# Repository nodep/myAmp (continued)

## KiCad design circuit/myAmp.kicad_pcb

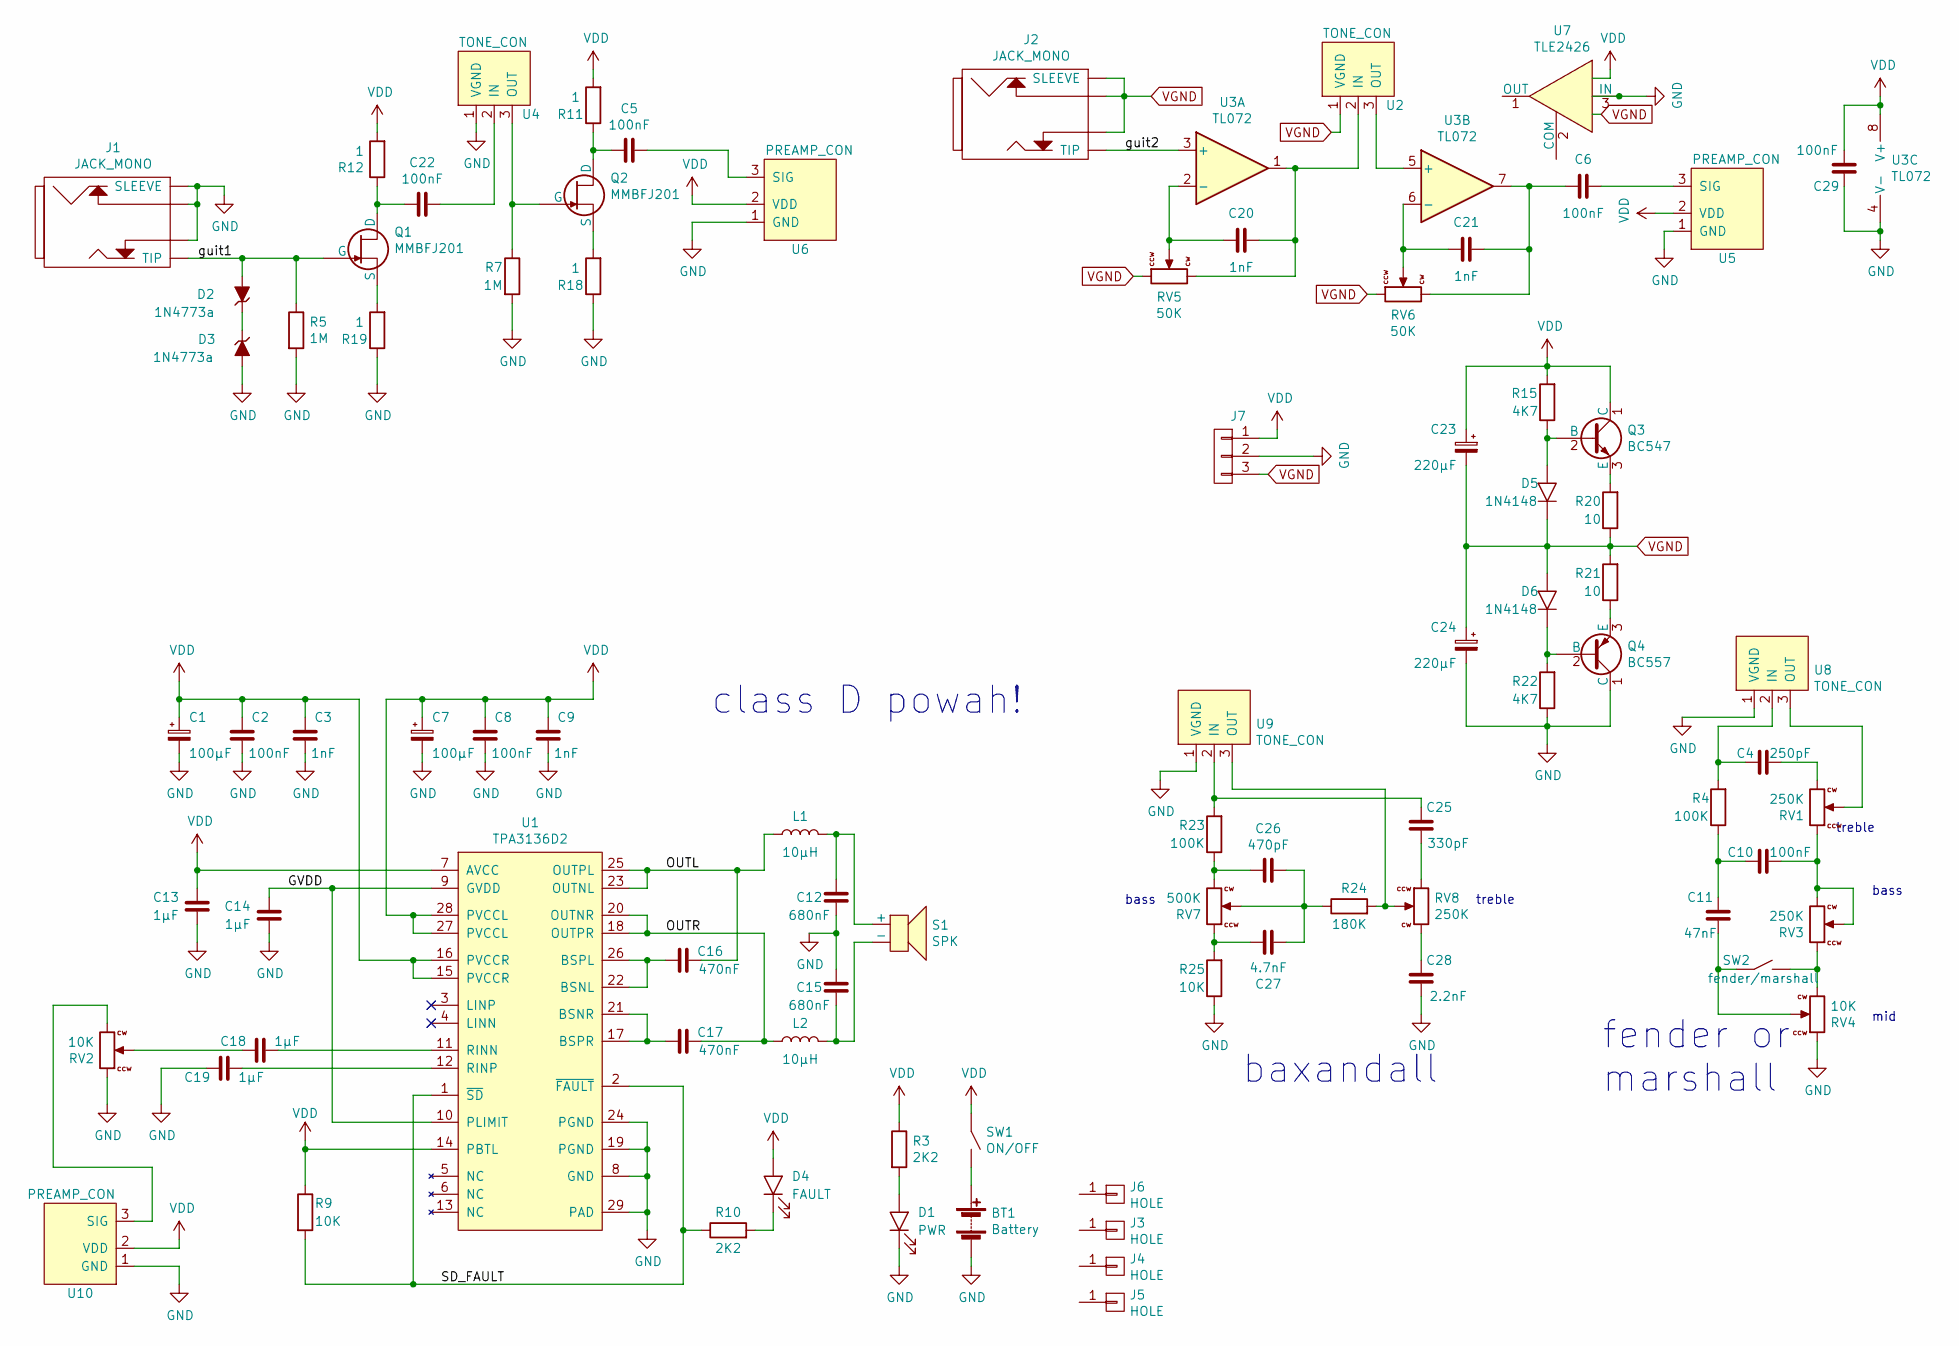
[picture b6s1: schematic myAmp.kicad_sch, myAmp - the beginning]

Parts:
BT1: Battery; BATTERY
C1, C7: 100μF; CPOL_D6.3_P2.5
C2, C8: 100nF; C_1206
C3, C9: 1nF; C_1206
C4: 250pF; C_5MM_1206
C5, C6, C10, C22, C29: 100nF; C_5MM_1206
C11: 47nF; C_5MM_1206
C12, C15: 680nF; C_FILM_5MM
C13, C14, C18, C19: 1μF; C_1206
C16, C17: 470nF; C_1206
C20, C21: 1nF; C_5MM_1206
C23, C24: 220μF; CPOL_D6.3_P2.5
C25: 330pF; C_5MM_1206
C26: 470pF; C_5MM_1206
C27: 4.7nF; C_5MM_1206
C28: 2.2nF; C_5MM_1206
D1: PWR; LED_D3.0mm
D2, D3: 1N4773a; DO41
D4: FAULT; LED_D3.0mm
D5, D6: 1N4148; DO35
J1, J2: JACK_MONO; JACK_CL13106
J3, J4, J5, J6: HOLE; MountingHole
J7: CONN_01X03; SPLITTER
L1, L2: 10μH; COILCRAFT_DR0810
Q1, Q2: MMBFJ201; SOT-23
Q3: BC547; TO-92_Inline_Wide
Q4: BC557; TO-92_Inline_Wide
R3, R10: 2K2; R_0805
R4, R23: 100K; R_10MM
R5, R7: 1M; R_10MM
R9: 10K; R_0805
R11, R12, R18, R19: 1; R_10MM
R15, R22: 4K7; R_0805
R20, R21: 10; R_0805
R24: 180K; R_10MM
R25: 10K; R_10MM
RV1, RV3, RV8: 250K; POT_VULGARIS
RV2, RV4: 10K; POT_VULGARIS
RV5, RV6: 50K; RPOT_RKT6V
RV7: 500K; POT_VULGARIS
S1: SPK; SPKR_5MM
SW1: ON/OFF; SW_TINY
SW2: fender/marshall; JUMPER
U1: TPA3136D2; HTSSOP-28_4.4x9.7mm_Pitch0.65mm_ThermalPad
U2, U4, U8, U9: TONE_CON
U3: TL072; SOIC-8_3.9x4.9mm_P1.27mm
U5, U6, U10: PREAMP_CON
U7: TLE2426; TO-92_Inline_Wide

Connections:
/GVDD: C14.1, U1.9 (GVDD), U1.10 (PLIMIT)
/OUTL: C16.1, L1.1, U1.23 (OUTNL), U1.25 (OUTPL)
/OUTR: C17.1, L2.1, U1.18 (OUTPR), U1.20 (OUTNR)
/SD_FAULT: R9.2, R10.1, U1.1 (~SD), U1.2 (~FAULT)
/guit1: D2.2 (A), J1.6 (TIP), Q1.3 (G), R5.1
/guit2: J2.6 (TIP), U3.3 (+)
unnamed: BT1.1 (+), SW1.2
unnamed: C4.1, RV1.3
unnamed: C4.2, R4.2, U8.2 (IN)
unnamed: C5.1, U6.3 (SIG)
unnamed: C5.2, Q2.1 (D), R11.1
unnamed: C6.1, U5.3 (SIG)
unnamed: C10.1, RV1.1, RV3.2, RV3.3
unnamed: C10.2, C11.2, R4.1
unnamed: C11.1, RV4.2, SW2.1
unnamed: C12.2, L1.2, S1.1 (+)
unnamed: C15.1, L2.2, S1.2 (-)
unnamed: C16.2, U1.22 (BSNL), U1.26 (BSPL)
unnamed: C17.2, U1.17 (BSPR), U1.21 (BSNR)
unnamed: C18.1, U1.11 (RINN)
unnamed: C18.2, RV2.2
unnamed: C19.1, U1.12 (RINP)
unnamed: C20.1, RV5.3, U2.2 (IN), U3.1
unnamed: C20.2, RV5.2, U3.2 (-)
unnamed: C6.2, C21.1, RV6.3, U3.7
unnamed: C21.2, RV6.2, U3.6 (-)
unnamed: C22.1, U4.2 (IN)
unnamed: C22.2, Q1.1 (D), R12.1
unnamed: C25.1, R23.2, U9.2 (IN)
unnamed: C25.2, RV8.1
unnamed: C26.1, C27.2, R24.1, RV7.2
unnamed: C26.2, R23.1, RV7.3
unnamed: C27.1, R25.2, RV7.1
unnamed: C28.1, RV8.3
unnamed: D1.2 (A), R3.2
unnamed: D2.1 (K), D3.1 (K)
unnamed: D4.1 (K), R10.2
unnamed: D5.2 (A), Q3.2 (B), R15.1
unnamed: D6.1 (K), Q4.2 (B), R22.2
unnamed: Q1.2 (S), R19.2
unnamed: Q2.2 (S), R18.2
unnamed: Q2.3 (G), R7.1, U4.3 (OUT)
unnamed: Q3.3 (E), R20.2
unnamed: Q4.3 (E), R21.1
unnamed: R24.2, RV8.2, U9.3 (OUT)
unnamed: RV1.2, U8.3 (OUT)
unnamed: RV2.3, U10.3 (SIG)
unnamed: RV3.1, RV4.3, SW2.2
unnamed: U2.3 (OUT), U3.5 (+)
VGND: C23.2, C24.1, D5.1 (K), D6.2 (A), J2.1, J2.3, J2.4 (SLEEVE), J7.3, R20.1, R21.2, RV5.1, RV6.1, U2.1 (VGND), U7.1 (OUT)

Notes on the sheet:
baxandall
class D powah!
bass
fender or marshall
mid
treble

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
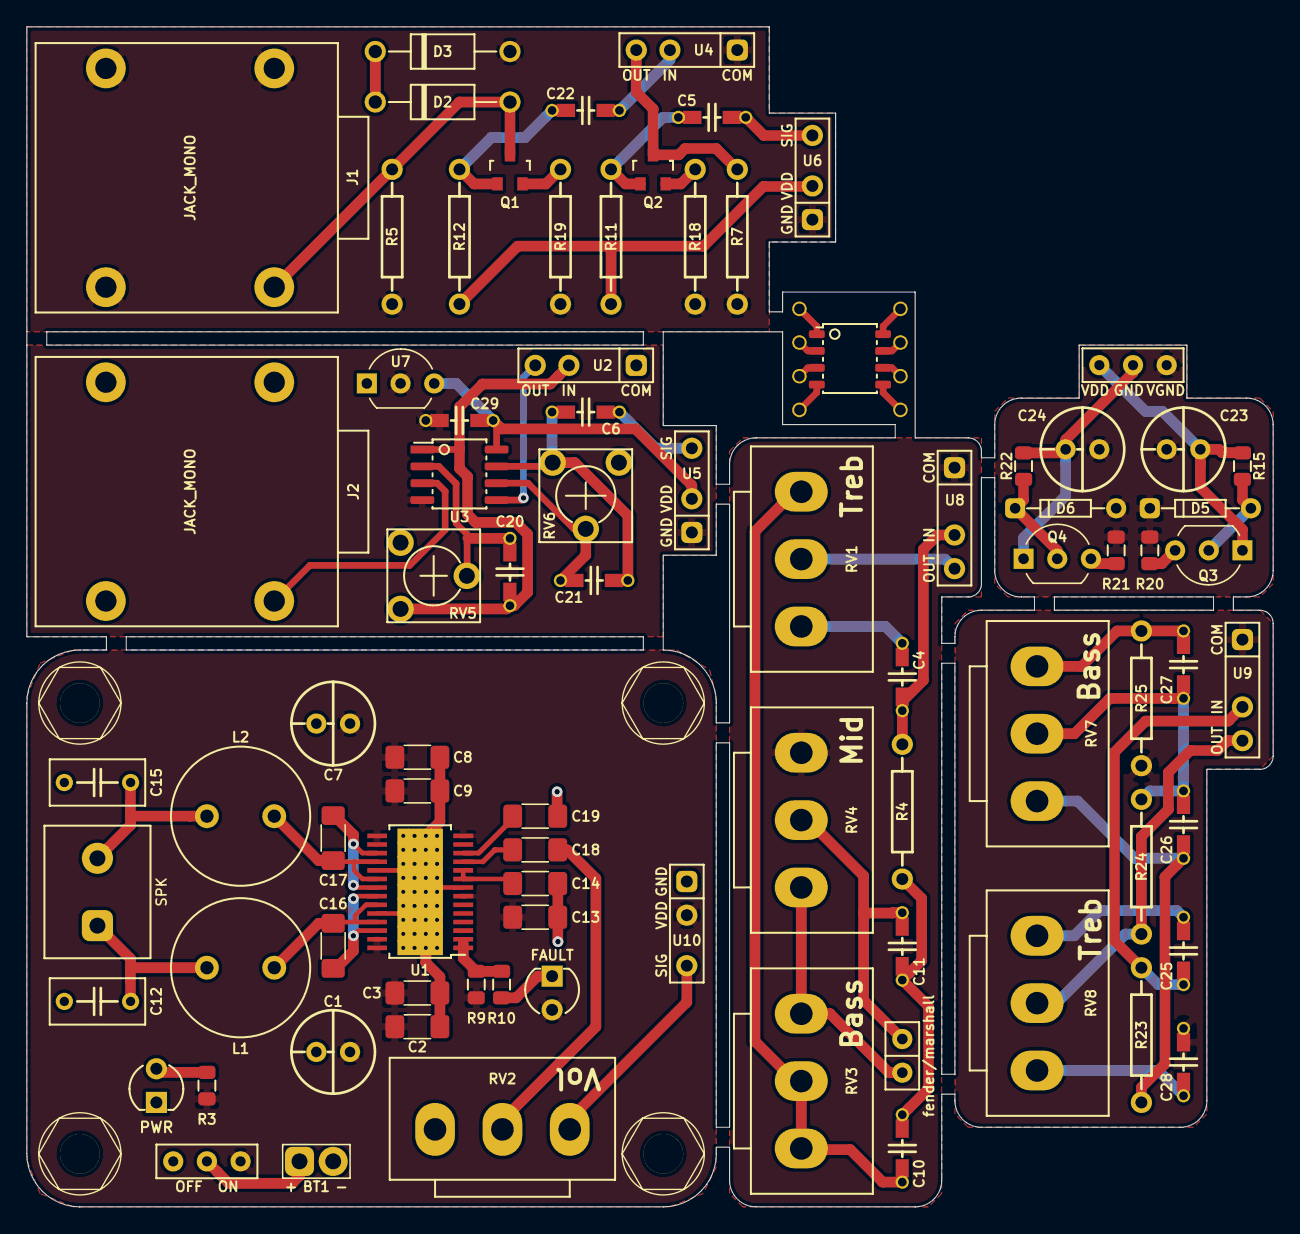
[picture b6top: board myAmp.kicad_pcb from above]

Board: 2 copper layers, 94.0 x 89.0 mm, 87 parts (0 on the bottom side), 52 nets.
